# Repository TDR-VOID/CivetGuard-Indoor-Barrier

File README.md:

# CivetGuard-Indoor-Barrier

## Overview
One of the most common problems faced by people living in rural areas is the intrusion of civets into their homes, particularly onto house roofs. Civets tend to visit during the night, causing damage to ceilings and disturbances with their nocturnal activities.
A common solution employed by residents is the use of high-wattage bulbs (flashlights) in the affected areas during the night. While effective, this solution consumes significant power, especially considering that civets may not be visited every night, leading to unnecessary energy expenditure.

The "CivetGuard Indoor Barrier" is designed to address this issue. It is a simple device that activates the flashlight only when motion is detected, eliminating the need to keep the light on throughout the night. Additionally, it features a Light Dependent Resistor (LDR) to ensure activation only in dark environments.

The device is built using the NodeMCU microcontroller development board and connects to the Firebase real-time database via the home Wi-Fi network. Real-time monitoring of the device's operation is possible through the Firebase database, allowing users to conveniently check its status without physically accessing the device, which is typically installed on the roof.

Users can track the number of flashlight activations within specific time periods (e.g., one night) to assess the device's efficiency. This data allows users to gauge whether the device is effectively working while minimizing unnecessary power consumption.

## Features
- **Power Efficiency:** The device ensures efficient power usage by activating the flashlight only when motion is detected, eliminating the need for continuous illumination throughout the night.
- **Real-time Monitoring with Database Integration:** The device utilizes Firebase database integration to enable real-time monitoring capabilities. Users can track flashlight activations and monitor LDR values remotely and instantly.
- **Multiple Operation Modes:**
    - Mode 1 [(Basic_Motion_Light)](Code/Basic_Motion_Light/Basic_Motion_Light.ino): The basic operating mode where the flashlight turns on upon detecting movement.
    - Mode 2 [(Motion_Ligth_With_Firebase_Data_Logger)](Code/Motion_Ligth_With_Firebase_Data_Logger/Motion_Ligth_With_Firebase_Data_Logger.ino): Extends Mode 1 functionality by logging the count of flashlight activations and the corresponding LDR values to the Firebase database.
    - Mode 3 [(Advanced_Motion_Control_With_Data_Logger)](Code/Advanced_Motion_Control_With_Data_Logger/Advanced_Motion_Control_With_Data_Logger.ino): Enhances functionality with advanced features, including activation based on the frequency of motion within a specified time frame, in addition to all features of Mode 2.    
- **Efficiency Analysis:** By analyzing the count of flashlight activations within specific time periods, users can draw conclusions regarding the device's efficiency and its ability to fulfil its intended purpose.

## Technical Details
- The BC547 NPN transistor operates as a switch, with the base connected to the microcontroller output pin (D2) via a resistor.
- An IN4007 diode is connected to stop the back EMF of the relay, specifically to protect the switching transistor.
- The circuit is powered through the NodeMCU Vin pin(5V, 1.5A).
- The PIR sensor is connected to the D1 digital pin, and the LDR is connected to the A0 analogue pin for the inputs.

Note: In some cases, the Light Dependent Resistor (LDR) may not be necessary, as the device is typically installed in a dark area.

<details>
<summary>Circuit Diagrams</summary>
  <div style="display: flex; justify-content: center;">

</div>
</details>

<details>
<summary>Firebase Realtime DB</summary>
  <div style="display: flex; justify-content: center;">
  
</div>
</details>

## Components Used

- NodeMCU
- PIR Motion Sensor
- LDR
- Transistor (BC547)
- Flashlight
  
<br />

## License

[MIT License](LICENSE)

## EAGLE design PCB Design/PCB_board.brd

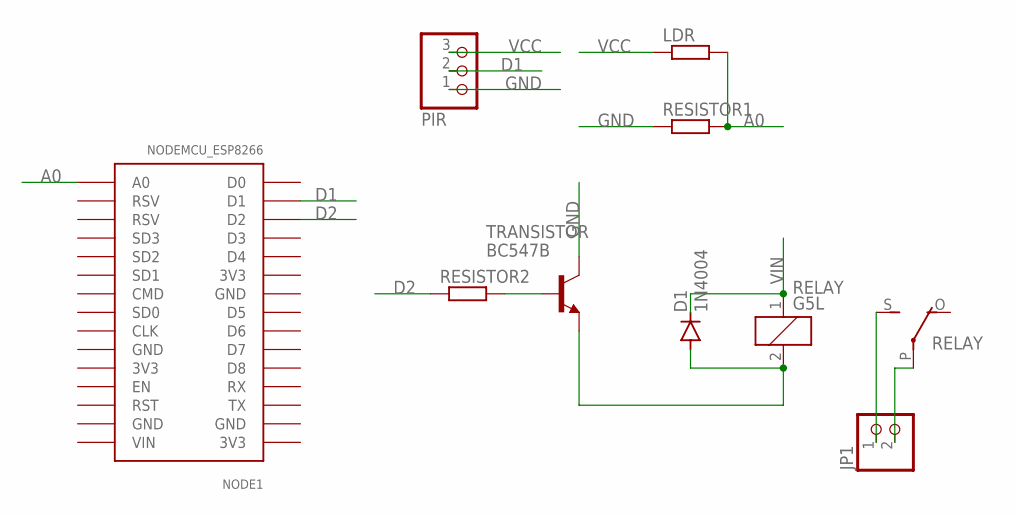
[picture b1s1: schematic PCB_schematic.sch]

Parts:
D1: 1N4004; DO41-10
JP1: PINHD-1X2; 1X02
LDR: R-EU_0204/7; 0204/7
NODE1: NODEMCU_ESP8266
PIR: PINHD-1X3; 1X03
RELAY: G5L; G5LE
RESISTOR1, RESISTOR2: R-EU_0204/7; 0204/7
TRANSISTOR: BC547B; TO92

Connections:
3V3: NODE1.3V3@1 (3V3), NODE1.3V3@2 (3V3), NODE1.3V3@3 (3V3)
A0: LDR.2, NODE1.A0, RESISTOR1.2
D1: NODE1.D1, PIR.2
D2: NODE1.D2, RESISTOR2.1
GND: NODE1.GND@1 (GND), NODE1.GND@2 (GND), NODE1.GND@3 (GND), NODE1.GND@4 (GND), PIR.1, RESISTOR1.1, TRANSISTOR.3 (C)
unnamed: JP1.1, RELAY.S
unnamed: D1.A, RELAY.2, TRANSISTOR.1 (E)
unnamed: RESISTOR2.2, TRANSISTOR.2 (B)
unnamed: JP1.2, RELAY.P
VCC: LDR.1, PIR.3
VIN: D1.C, NODE1.VIN, RELAY.1

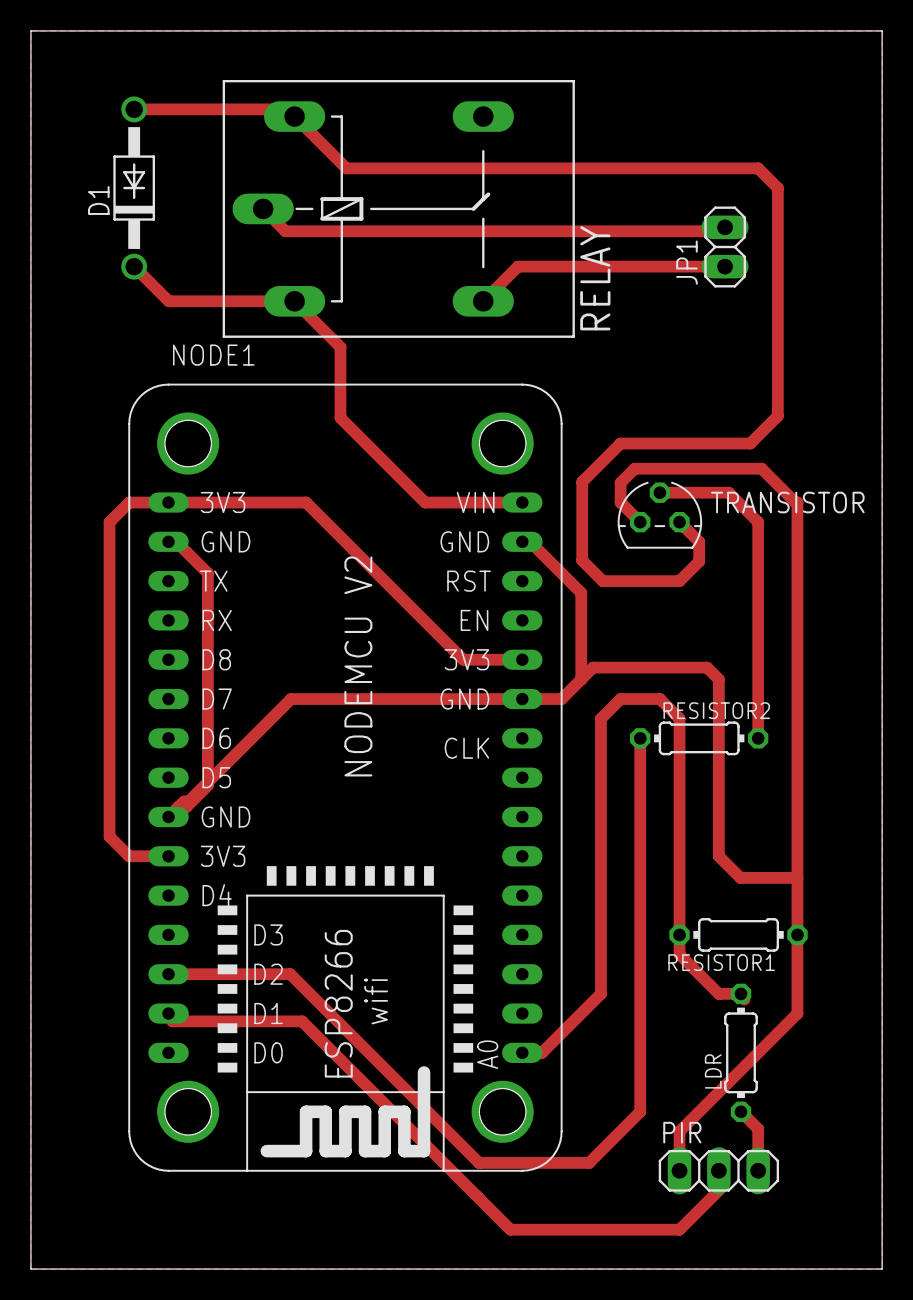
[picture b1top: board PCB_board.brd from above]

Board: 2 copper layers, 55.0 x 80.0 mm, 9 parts (0 on the bottom side), 11 nets.

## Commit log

2024-04-24 Create m
2024-08-31 Create LICENSE
